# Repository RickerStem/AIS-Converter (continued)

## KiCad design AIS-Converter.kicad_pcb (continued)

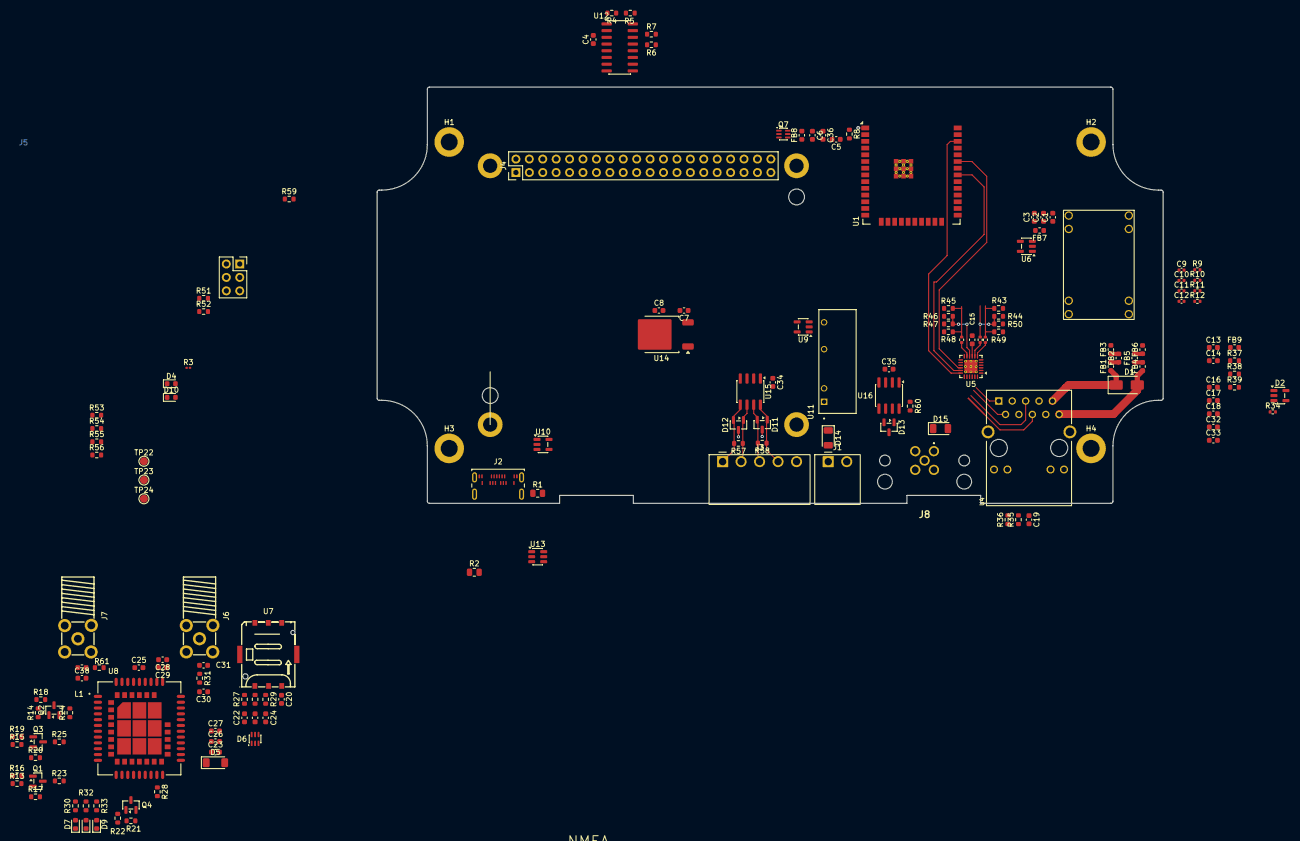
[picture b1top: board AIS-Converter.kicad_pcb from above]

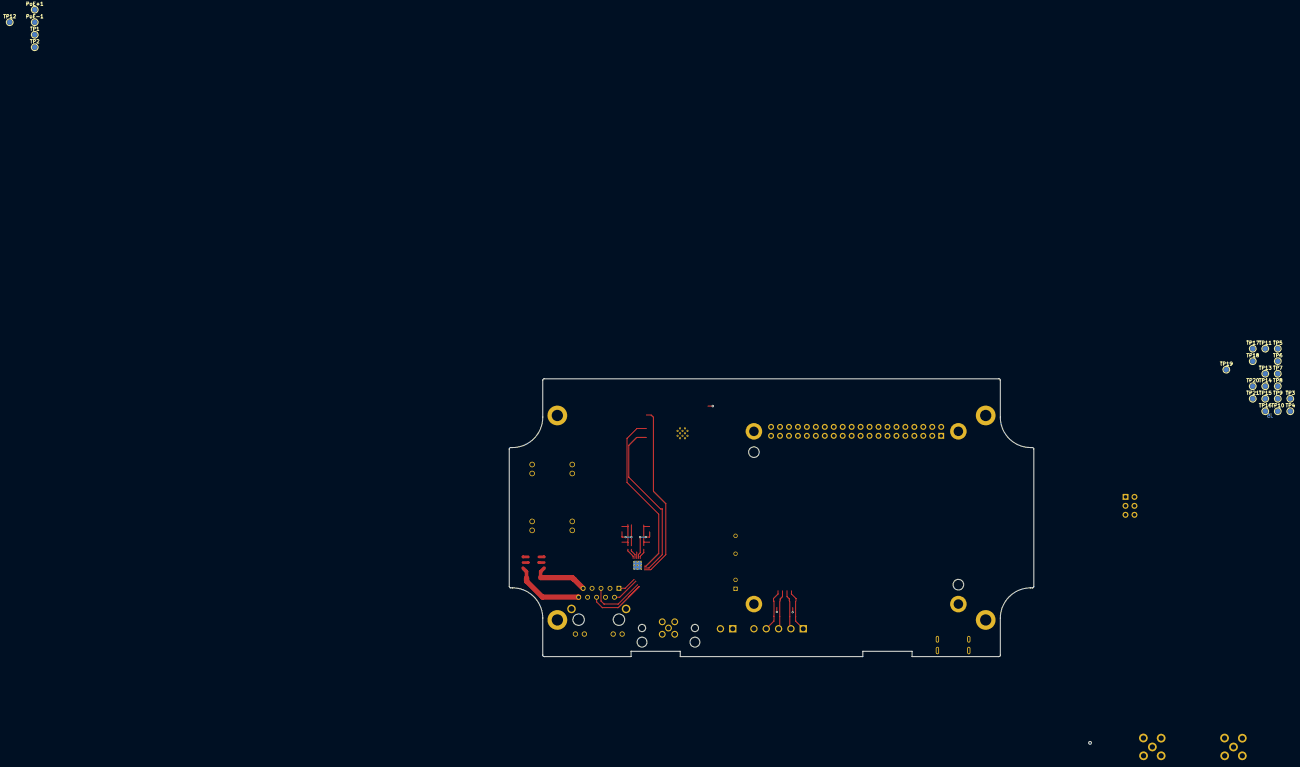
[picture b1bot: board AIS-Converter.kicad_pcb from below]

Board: 4 copper layers, 148.8 x 78.8 mm, 182 parts (23 on the bottom side), 115 nets.

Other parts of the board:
FF: RPI5_Form_Factor; RPI5_Form_Factor_AIS_Project

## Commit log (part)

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2026-06-05 Initial KiCad files new project
2026-06-05 Fixed some lib files
2026-06-16 Adding hierarchical blocks
2026-06-30 progress save
